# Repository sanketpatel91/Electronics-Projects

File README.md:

# Electronics-Projects

## 1. Real Time Clock Using Arduino & 7 Segment Display HHMM
## 2. Date, Day, Real Time Clock Using Arduino & LCD Display

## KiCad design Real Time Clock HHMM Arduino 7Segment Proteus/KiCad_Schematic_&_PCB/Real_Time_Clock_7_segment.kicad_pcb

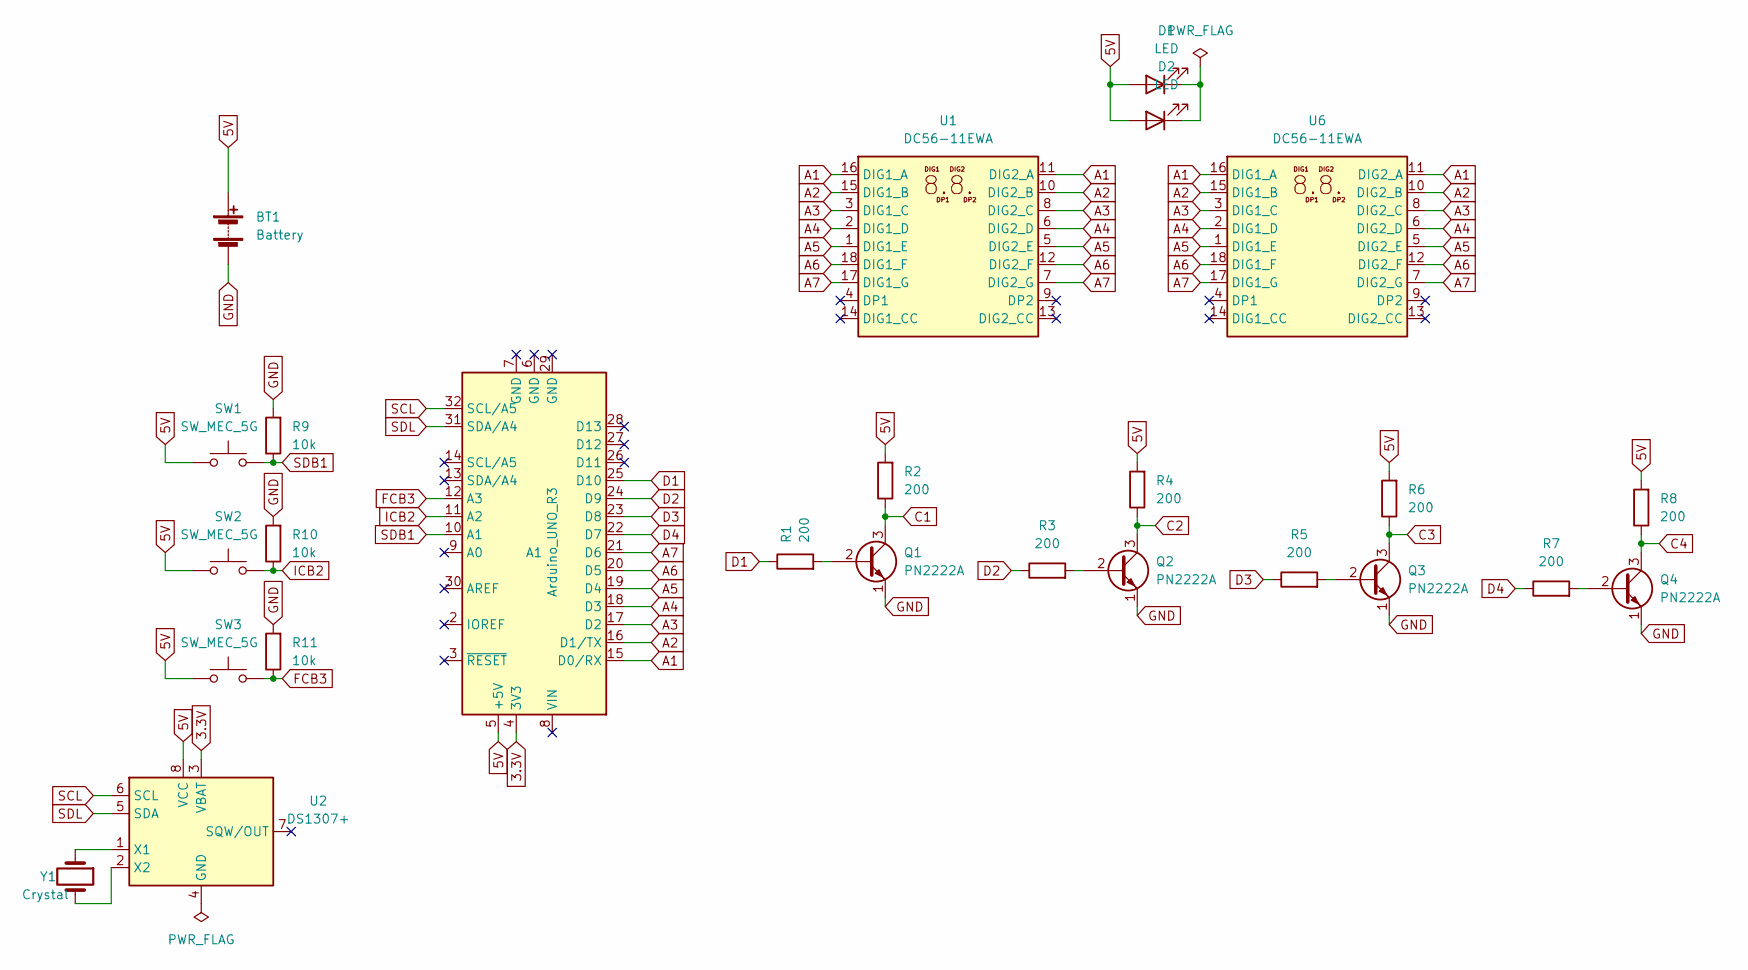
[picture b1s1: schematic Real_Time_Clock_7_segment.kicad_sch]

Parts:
A1: Arduino_UNO_R3; Arduino_UNO_R3_WithMountingHoles
BT1: Battery; BatteryHolder_MPD_BA9VPC_1xPP3
D1, D2: LED; LED_D3.0mm
Q1, Q2, Q3, Q4: PN2222A; TO-92_Inline
R1, R2, R3, R4, R5, R6, R7, R8: 200; R_Axial_DIN0204_L3.6mm_D1.6mm_P1.90mm_Vertical
R9, R10, R11: 10k; R_Axial_DIN0204_L3.6mm_D1.6mm_P1.90mm_Vertical
SW1, SW2, SW3: SW_MEC_5G; SW_MEC_5GSH9
U1, U6: DC56-11EWA; DA56-11SURKWA
U2: DS1307+; DIP-8_W7.62mm
Y1: Crystal; Crystal_AT310_D3.0mm_L10.0mm_Horizontal

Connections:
3.3V: A1.4 (3V3), U2.3 (VBAT)
5V: A1.5 (+5V), BT1.1 (+), D1.2 (A), D2.2 (A), R2.2, R4.2, R6.2, R8.2, SW1.1 (A), SW1.2 (A), SW2.1 (A), SW2.2 (A), SW3.1 (A), SW3.2 (A), U2.8 (VCC)
A1: A1.15 (D0/RX), U1.11 (DIG2_A), U1.16 (DIG1_A), U6.11 (DIG2_A), U6.16 (DIG1_A)
A2: A1.16 (D1/TX), U1.10 (DIG2_B), U1.15 (DIG1_B), U6.10 (DIG2_B), U6.15 (DIG1_B)
A3: A1.17 (D2), U1.3 (DIG1_C), U1.8 (DIG2_C), U6.3 (DIG1_C), U6.8 (DIG2_C)
A4: A1.18 (D3), U1.2 (DIG1_D), U1.6 (DIG2_D), U6.2 (DIG1_D), U6.6 (DIG2_D)
A5: A1.19 (D4), U1.1 (DIG1_E), U1.5 (DIG2_E), U6.1 (DIG1_E), U6.5 (DIG2_E)
A6: A1.20 (D5), U1.12 (DIG2_F), U1.18 (DIG1_F), U6.12 (DIG2_F), U6.18 (DIG1_F)
A7: A1.21 (D6), U1.7 (DIG2_G), U1.17 (DIG1_G), U6.7 (DIG2_G), U6.17 (DIG1_G)
C1: Q1.3 (C), R2.1
C2: Q2.3 (C), R4.1
C3: Q3.3 (C), R6.1
C4: Q4.3 (C), R8.1
D1: A1.25 (D10), R1.1
D2: A1.24 (D9), R3.1
D3: A1.23 (D8), R5.1
D4: A1.22 (D7), R7.1
FCB3: A1.12 (A3), R11.1, SW3.3 (B), SW3.4 (B)
GND: BT1.2 (-), Q1.1 (E), Q2.1 (E), Q3.1 (E), Q4.1 (E), R9.2, R10.2, R11.2
ICB2: A1.11 (A2), R10.1, SW2.3 (B), SW2.4 (B)
unnamed: D1.1 (K), D2.1 (K)
unnamed: Q1.2 (B), R1.2
unnamed: Q2.2 (B), R3.2
unnamed: Q3.2 (B), R5.2
unnamed: Q4.2 (B), R7.2
unnamed: U2.1 (X1), Y1.1
unnamed: U2.2 (X2), Y1.2
SCL: A1.32 (SCL/A5), U2.6 (SCL)
SDB1: A1.10 (A1), R9.1, SW1.3 (B), SW1.4 (B)
SDL: A1.31 (SDA/A4), U2.5 (SDA)

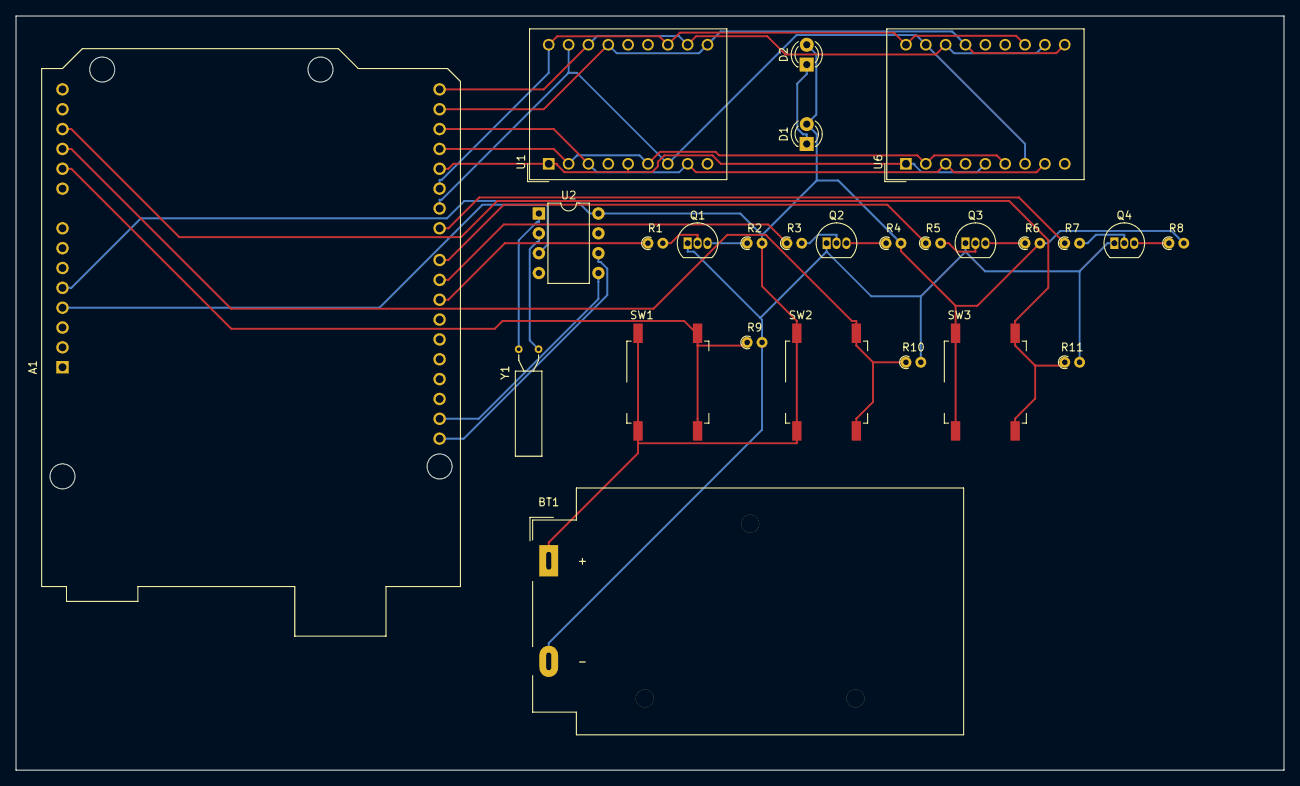
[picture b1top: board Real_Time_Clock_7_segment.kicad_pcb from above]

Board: 2 copper layers, 162.3 x 96.5 mm, 26 parts (0 on the bottom side), 30 nets.

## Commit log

2022-02-19 Add files via upload
    19-Feb-2022
    Arduino and Proteus project
    4 Digit 7 Segment Display rela time clock using RTC DS1307 : HHMM
2022-03-04 Updated code
2022-03-04 renamed images
2022-03-04 Added Doxygen File and html
2022-03-04 Updated Doxygen documentation
2022-03-05 Added LCD Project: Date Day ClockTime Using Arduino & LCD
2022-03-05 Replaced Not Gate logic with Transistor
2022-03-06 Added KiCad 6.0 Schematic ,PCB and Project Files
